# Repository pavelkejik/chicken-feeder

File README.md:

# Smart Chicken Feeder
_An ESP32-powered accessory for automated feed control_

## Overview
This smart feeder is part of the Automated Chicken Coop Ecosystem. It operates wirelessly and autonomously to dispense food based on schedule, user commands, or weight target.

Powered by a battery-friendly ESP32-C3 and connected via **ESP-NOW** to the main coop door (gateway), the feeder ensures reliable long-term operation and seamless integration into the larger coop management system.

---

## Features
- **Scheduled feeding** with daily times and portion sizes
- **Feed-to-weight** mode using integrated load-cell
- **ESP-NOW** communication for ultra-low power use
- Battery-powered, optimized for deep sleep
- OTA firmware updates via the coop door gateway
- Status reported via MQTT (via gateway) and visible in Web UI

---

## Hardware
| Component | Purpose |
|----------|---------|
| ESP32-C3 | Low-power microcontroller with Wi-Fi and ESP-NOW |
| Load Cell + HX711 | Measure feed weight in grams |
| Servo Motor | Open/close feed flap |
| 18650 Li-Ion + Charger | Power supply for standalone use |

All components are enclosed in a 3D-printable case. STL files and PCB design are in the `hw/` directory.

---

## Communication
### ESP-NOW
- Feeder registers with the door (gateway)

### MQTT (via Gateway)
```text
<base_topic>/devices/<feeder-id>/state/weight_g        = 175
<base_topic>/devices/<feeder-id>/set/feed_g            ← 50
<base_topic>/devices/<feeder-id>/set/mode              ← "schedule" | "weight"
```

---

## Power Management
- Sleeps between operations using deep sleep
- Wakeup on timer or servo/feed command
- Runtime per charge depends on feeding frequency

---

## OTA Updates
- Triggered remotely via the coop door
- Uses ESP-NOW for wire-free, zero-setup OTA

---

## Getting Started
1. Flash firmware using PlatformIO:
   ```bash
   cd firmware
   pio run -t upload
   ```
2. Power up the feeder and press the pairing button once.
3. In the Web UI (at `dvirka.local`), go to **Accessories > New > Pair**.
4. Once connected, it will appear in the dashboard.

---

## Author
**Pavel Kejík**  
Part of the Automated Coop Ecosystem – see main project: [chicken-door](https://github.com/pavelkejik/chicken-door)

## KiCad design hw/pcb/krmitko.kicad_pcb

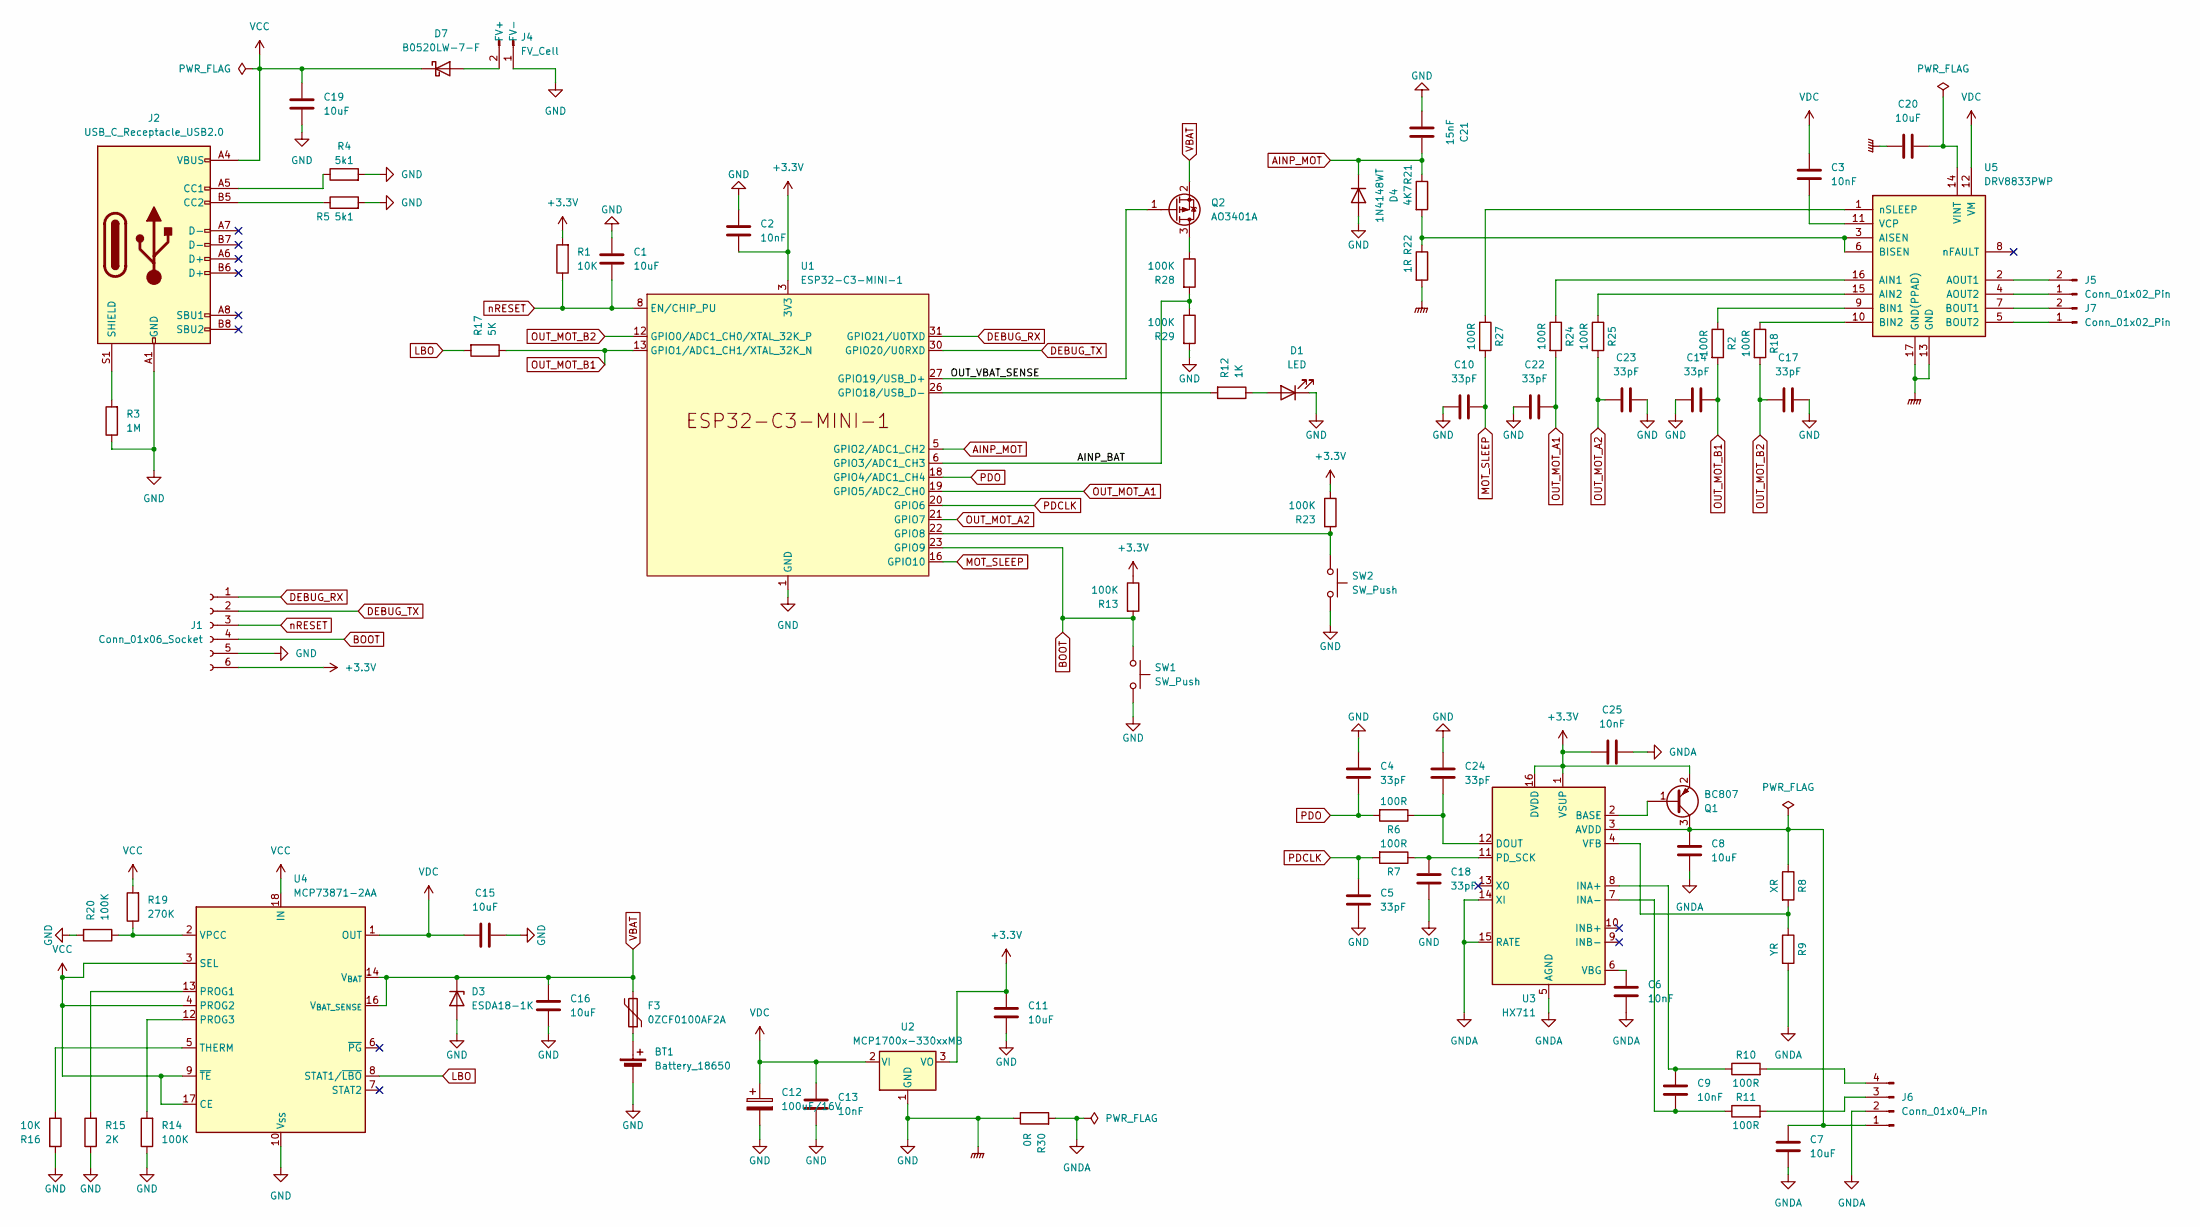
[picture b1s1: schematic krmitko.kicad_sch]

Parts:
BT1: Battery_18650; BatteryHolder_MPD_BH-18650-PC2
C1, C7, C8, C11, C15, C16, C19, C20: 10uF; C_0805_2012Metric_Pad1.18x1.45mm_HandSolder
C2, C3, C6, C9, C13, C25: 10nF; C_0805_2012Metric_Pad1.18x1.45mm_HandSolder
C4, C5, C10, C14, C17, C18, C22, C23, C24: 33pF; C_0805_2012Metric_Pad1.18x1.45mm_HandSolder
C12: 100uF/16V; CP_Elec_6.3x7.7
C21: 15nF; C_0805_2012Metric_Pad1.18x1.45mm_HandSolder
D1: LED; LED_1210_3225Metric_Pad1.42x2.65mm_HandSolder
D3: ESDA18-1K; D_SMA
D4: 1N4148WT; D_SOD-123F
D7: B0520LW-7-F; D_SOD-123
F3: 0ZCF0100AF2A; Fuse_2920_7451Metric_Pad2.10x5.45mm_HandSolder
J1: Conn_01x06_Socket; PinHeader_1x06_P2.54mm_Vertical
J2: USB_C_Receptacle_USB2.0; USB_C_Receptacle_GCT_USB4105-xx-A_16P_TopMnt_Horizontal
J4: FV_Cell; Molex_KK-254_AE-6410-02A_1x02_P2.54mm_Vertical
J5, J7: Conn_01x02_Pin; Molex_KK-254_AE-6410-02A_1x02_P2.54mm_Vertical
J6: Conn_01x04_Pin; Molex_KK-254_AE-6410-04A_1x04_P2.54mm_Vertical
Q1: BC807; SOT-23
Q2: AO3401A; SOT-23
R1, R16: 10K; R_0805_2012Metric_Pad1.20x1.40mm_HandSolder
R2, R6, R7, R10, R11, R18, R24, R25, R27: 100R; R_0805_2012Metric_Pad1.20x1.40mm_HandSolder
R3: 1M; R_0805_2012Metric_Pad1.20x1.40mm_HandSolder
R4, R5: 5k1; R_0805_2012Metric_Pad1.20x1.40mm_HandSolder
R8: XR; R_0805_2012Metric_Pad1.20x1.40mm_HandSolder
R9: YR; R_0805_2012Metric_Pad1.20x1.40mm_HandSolder
R12: 1K; R_0805_2012Metric_Pad1.20x1.40mm_HandSolder
R13, R14, R20, R23, R28, R29: 100K; R_0805_2012Metric_Pad1.20x1.40mm_HandSolder
R15: 2K; R_0805_2012Metric_Pad1.20x1.40mm_HandSolder
R17: 5K; R_0805_2012Metric_Pad1.20x1.40mm_HandSolder
R19: 270K; R_0805_2012Metric_Pad1.20x1.40mm_HandSolder
R21: 4K7; R_0805_2012Metric_Pad1.20x1.40mm_HandSolder
R22: 1R; R_0805_2012Metric_Pad1.20x1.40mm_HandSolder
R30: 0R; R_0805_2012Metric_Pad1.20x1.40mm_HandSolder
SW1, SW2: SW_Push; SW_Tactile_SPST_Angled_PTS645Vx58-2LFS
U1: ESP32-C3-MINI-1
U2: MCP1700x-330xxMB; SOT-89-3
U3: HX711; SOP-16_3.9x9.9mm_P1.27mm
U4: MCP73871-2AA; QFN-20-1EP_4x4mm_P0.5mm_EP2.5x2.5mm
U5: DRV8833PWP; HTSSOP-16-1EP_4.4x5mm_P0.65mm_EP3.4x5mm_Mask2.46x2.31mm_The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

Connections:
+3.3V: C2.2, C11.2, C25.2, J1.6, Q1.2 (E), R1.2, R13.1, R23.1, U1.3 (3V3), U2.3 (VO), U3.1 (VSUP), U3.16 (DVDD)
/AINP_BAT: R28.2, R29.1, U1.6 (GPIO3/ADC1_CH3)
/OUT_VBAT_SENSE: Q2.1 (G), U1.27 (GPIO19/USB_D+)
AINP_MOT: C21.2, D4.1 (K), R21.1, U1.5 (GPIO2/ADC1_CH2)
BOOT: J1.4, R13.2, SW1.1, U1.23 (GPIO9)
DEBUG_RX: J1.1, U1.31 (GPIO21/U0TXD)
DEBUG_TX: J1.2, U1.30 (GPIO20/U0RXD)
GND: BT1.2 (-), C1.1, C2.1, C4.1, C5.2, C10.1, C11.1, C12.2, C13.1, C14.1, C15.2, C16.1, C17.2, C18.2, C19.2, C20.1, C21.1, C22.1, C23.2, C24.1, D1.1 (K), D3.2 (A), D4.2 (A), J1.5, J2.A1 (GND), J2.A12 (GND), J2.B1 (GND), J2.B12 (GND), J4.1 (FV-), R3.1, R4.2, R5.2, R14.1, R15.1, R16.2, R20.2, R22.2, R29.2, R30.1, SW1.2, SW2.2, U1.1 (GND), U1.2 (GND), U1.11 (GND), U1.14 (GND), U1.36 (GND), U1.37 (GND), U1.38 (GND), U1.39 (GND), U1.40 (GND), U1.41 (GND), U1.42 (GND), U1.43 (GND), U1.44 (GND), U1.45 (GND), U1.46 (GND), U1.47 (GND), U1.48 (GND), U1.49 (GND), U1.50 (GND), U1.51 (GND), U1.52 (GND), U1.53 (GND), U2.1 (GND), U4.10 (V_{SS}), U4.11 (V_{SS}), U4.21 (V_{SS}), U5.13 (GND), U5.17 (GND(PPAD))
GNDA: C6.1, C7.1, C8.1, C25.1, J6.2, R9.2, R30.2, U3.5 (AGND), U3.14 (XI), U3.15 (RATE)
LBO: R17.2, U4.8 (STAT1/~LBO)
MOT_SLEEP: C10.2, R27.2, U1.16 (GPIO10)
unnamed: BT1.1 (+), F3.1
unnamed: D1.2 (A), R12.1
unnamed: D7.2 (A), J4.2 (FV+)
unnamed: J2.A5 (CC1), R4.1
unnamed: J2.B5 (CC2), R5.1
unnamed: J2.S1 (SHIELD), R3.2
unnamed: J5.1, U5.4 (AOUT2)
unnamed: J5.2, U5.2 (AOUT1)
unnamed: C7.2, C8.2, J6.1, Q1.3 (C), R8.1, U3.3 (AVDD)
unnamed: J6.3, R11.2
unnamed: J6.4, R10.2
unnamed: J7.1, U5.5 (BOUT2)
unnamed: J7.2, U5.7 (BOUT1)
unnamed: Q1.1 (B), U3.2 (BASE)
unnamed: Q2.3 (D), R28.1
unnamed: R23.2, SW2.1, U1.22 (GPIO8)
unnamed: R12.2, U1.26 (GPIO18/USB_D-)
unnamed: C24.2, R6.1, U3.12 (DOUT)
unnamed: C9.2, R10.1, U3.8 (INA+)
unnamed: C9.1, R11.1, U3.7 (INA-)
unnamed: C18.1, R7.1, U3.11 (PD_SCK)
unnamed: C6.2, U3.6 (VBG)
unnamed: R8.2, R9.1, U3.4 (VFB)
unnamed: R15.2, U4.13 (PROG1)
unnamed: R14.2, U4.12 (PROG3)
unnamed: R16.1, U4.5 (THERM)
unnamed: R19.1, R20.1, U4.2 (VPCC)
unnamed: R24.1, U5.16 (AIN1)
unnamed: R25.1, U5.15 (AIN2)
unnamed: R21.2, R22.1, U5.3 (AISEN), U5.6 (BISEN)
unnamed: R2.1, U5.9 (BIN1)
unnamed: R18.1, U5.10 (BIN2)
unnamed: C3.1, U5.11 (VCP)
unnamed: C20.2, U5.14 (VINT)
unnamed: R27.1, U5.1 (nSLEEP)
OUT_MOT_A1: C22.2, R24.2, U1.19 (GPIO5/ADC2_CH0)
OUT_MOT_A2: C23.1, R25.2, U1.21 (GPIO7)
OUT_MOT_B1: C14.2, R2.2, R17.1, U1.13 (GPIO1/ADC1_CH1/XTAL_32K_N)
OUT_MOT_B2: C17.1, R18.2, U1.12 (GPIO0/ADC1_CH0/XTAL_32K_P)
PDCLK: C5.1, R7.2, U1.20 (GPIO6)
PDO: C4.2, R6.2, U1.18 (GPIO4/ADC1_CH4)
VBAT: C16.2, D3.1 (K), F3.2, Q2.2 (S), U4.14 (V_{BAT}), U4.15 (V_{BAT}), U4.16 (V_{BAT_SENSE})
VCC: C19.1, D7.1 (K), J2.A4 (VBUS), J2.A9 (VBUS), J2.B4 (VBUS), J2.B9 (VBUS), R19.2, U4.3 (SEL), U4.4 (PROG2), U4.9 (~TE), U4.17 (CE), U4.18 (IN), U4.19 (IN)
VDC: C3.2, C12.1, C13.2, C15.1, U2.2 (VI), U4.1 (OUT), U4.20 (OUT), U5.12 (VM)
nRESET: C1.2, J1.3, R1.1, U1.8 (EN/CHIP_PU)

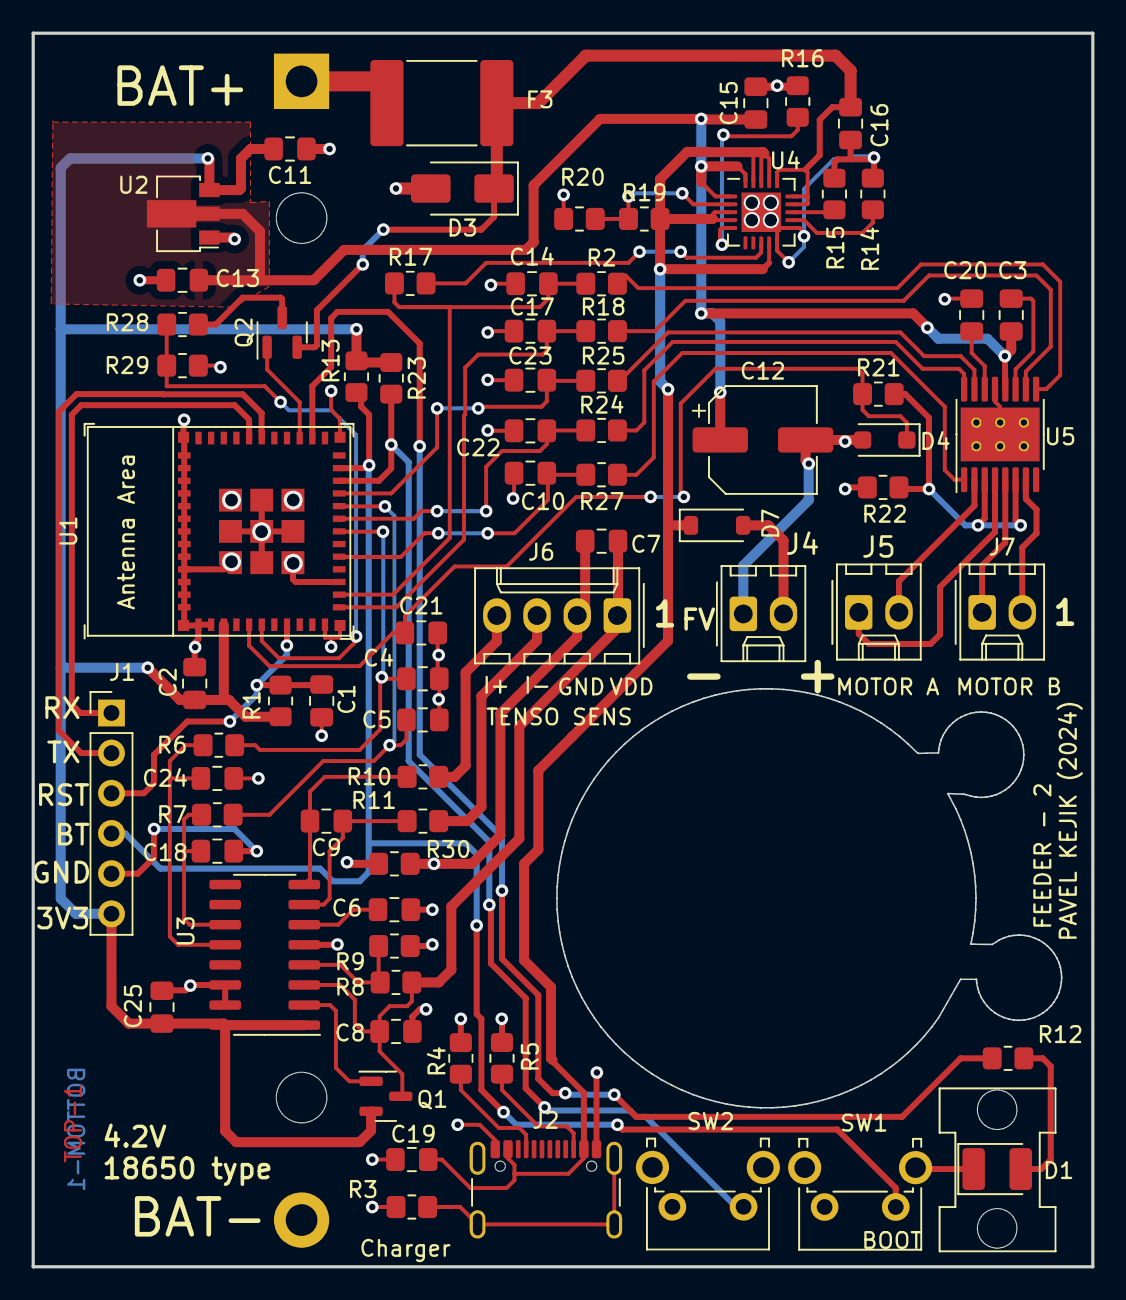
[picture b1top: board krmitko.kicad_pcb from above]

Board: 2 copper layers, 67.0 x 78.0 mm, 75 parts (1 on the bottom side), 56 nets.

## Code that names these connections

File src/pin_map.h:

/***********************************************************************
 * Filename: pin_map.h
 * Author: Pavel Kejik
 * Date: 2024-04-12
 * Description:
 *     Defines pin mappings for various components like 
 *     motor control, buttons and sensors.
 *
 ***********************************************************************/

#pragma once

#define MOT_A1 7
#define MOT_A2 5
#define MOT_SLEEP 10
#define MOT_ISENSE 2
#define BTN_1 8
#define BTN_2 9
#define BTN_WAKE 0
#define LED_R 18
#define LBO 1
#define PDCLK 6
#define PDO 4
#define BAT_AINP 3
#define BAT_NSENSE 19

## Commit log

2025-03-02 Initial commit of chicken feeder project
2025-04-23 Publish 3D-print files & KiCad sources
